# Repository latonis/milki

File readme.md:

# milki

Keyboard I want to designs

wip

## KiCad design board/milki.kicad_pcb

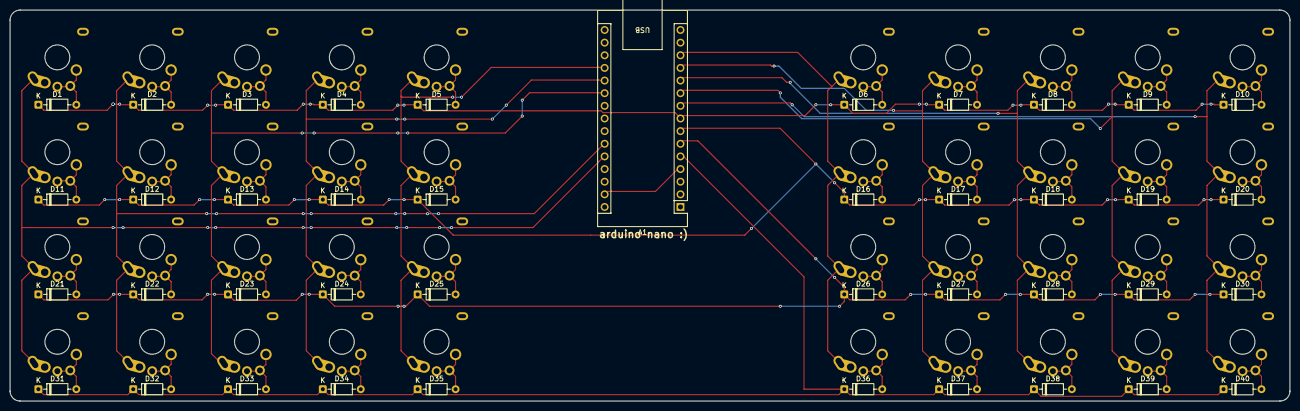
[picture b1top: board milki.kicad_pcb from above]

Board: 2 copper layers, 257.2 x 78.6 mm, 81 parts (0 on the bottom side), 55 nets.

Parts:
A1: Arduino_Nano_Every; Arduino_Nano
D1, D2, D3, D4, D5, D6, D7, D8, D9, D10, D11, D12, D13, D14, D15, D16, D17, D18, D19, D20, D21, D22, D23, D24, D25, D26, D27, D28, D29, D30, D31, D32, D33, D34, D35, D36, D37, D38, D39, D40: 1N4148; D_DO-35_SOD27_P7.62mm_Horizontal
MX1, MX2, MX3, MX4, MX5, MX6, MX7, MX8, MX9, MX10, MX11, MX12, MX13, MX14, MX15, MX16, MX17, MX18, MX19, MX20, MX21, MX22, MX23, MX24, MX25, MX26, MX27, MX28, MX29, MX30, MX31, MX32, MX33, MX34, MX35, MX36, MX37, MX38, MX39, MX40: MX_SW_solder; Low Profile GC plus MX

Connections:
/Col 0: A1.26 (A7), MX1.1, MX11.1, MX21.1, MX31.1
/Col 1: A1.25 (A6), MX2.1, MX12.1, MX22.1, MX32.1
/Col 2: A1.21 (A2), MX3.1, MX13.1, MX23.1, MX33.1
/Col 3: A1.20 (A1), MX4.1, MX14.1, MX24.1, MX34.1
/Col 4: A1.19 (A0), MX5.1, MX15.1, MX25.1, MX35.1
/Col 5: A1.13 (D10), MX6.1, MX16.1, MX26.1, MX36.1
/Col 6: A1.12 (D9), MX7.1, MX17.1, MX27.1, MX37.1
/Col 7: A1.11 (D8), MX8.1, MX18.1, MX28.1, MX38.1
/Col 8: A1.10 (D7), MX9.1, MX19.1, MX29.1, MX39.1
/Col 9: A1.9 (D6), MX10.1, MX20.1, MX30.1, MX40.1
/Row 0: A1.8 (D5), D1.1 (K), D2.1 (K), D3.1 (K), D4.1 (K), D5.1 (K), D6.1 (K), D7.1 (K), D8.1 (K), D9.1 (K), D10.1 (K)
/Row 1: A1.7 (D4), D11.1 (K), D12.1 (K), D13.1 (K), D14.1 (K), D15.1 (K), D16.1 (K), D17.1 (K), D18.1 (K), D19.1 (K), D20.1 (K)
/Row 2: A1.6 (D3), D21.1 (K), D22.1 (K), D23.1 (K), D24.1 (K), D25.1 (K), D26.1 (K), D27.1 (K), D28.1 (K), D29.1 (K), D30.1 (K)
/Row 3: A1.5 (D2), D31.1 (K), D32.1 (K), D33.1 (K), D34.1 (K), D35.1 (K), D36.1 (K), D37.1 (K), D38.1 (K), D39.1 (K), D40.1 (K)
unnamed: A1.4 (GND), A1.29 (GND)
unnamed: D1.2 (A), MX1.2
unnamed: D2.2 (A), MX2.2
unnamed: D3.2 (A), MX3.2
unnamed: D4.2 (A), MX4.2
unnamed: D5.2 (A), MX5.2
unnamed: D6.2 (A), MX6.2
unnamed: D7.2 (A), MX7.2
unnamed: D8.2 (A), MX8.2
unnamed: D9.2 (A), MX9.2
unnamed: D10.2 (A), MX10.2
unnamed: D11.2 (A), MX11.2
unnamed: D12.2 (A), MX12.2
unnamed: D13.2 (A), MX13.2
unnamed: D14.2 (A), MX14.2
unnamed: D15.2 (A), MX15.2
unnamed: D16.2 (A), MX16.2
unnamed: D17.2 (A), MX17.2
unnamed: D18.2 (A), MX18.2
unnamed: D19.2 (A), MX19.2
unnamed: D20.2 (A), MX20.2
unnamed: D21.2 (A), MX21.2
unnamed: D22.2 (A), MX22.2
unnamed: D23.2 (A), MX23.2
unnamed: D24.2 (A), MX24.2
unnamed: D25.2 (A), MX25.2
unnamed: D26.2 (A), MX26.2
unnamed: D27.2 (A), MX27.2
unnamed: D28.2 (A), MX28.2
unnamed: D29.2 (A), MX29.2
unnamed: D30.2 (A), MX30.2
unnamed: D31.2 (A), MX31.2
unnamed: D32.2 (A), MX32.2
unnamed: D33.2 (A), MX33.2
unnamed: D34.2 (A), MX34.2
unnamed: D35.2 (A), MX35.2
unnamed: D36.2 (A), MX36.2
unnamed: D37.2 (A), MX37.2
unnamed: D38.2 (A), MX38.2
unnamed: D39.2 (A), MX39.2
unnamed: D40.2 (A), MX40.2

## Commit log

2026-02-16 docs: readme
2026-02-16 chore: gitignore
2026-02-16 feat: start of board design
2026-02-20 i've switched up
2026-02-21 all wired up
